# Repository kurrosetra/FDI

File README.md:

# FDI
Front Destination Indicator

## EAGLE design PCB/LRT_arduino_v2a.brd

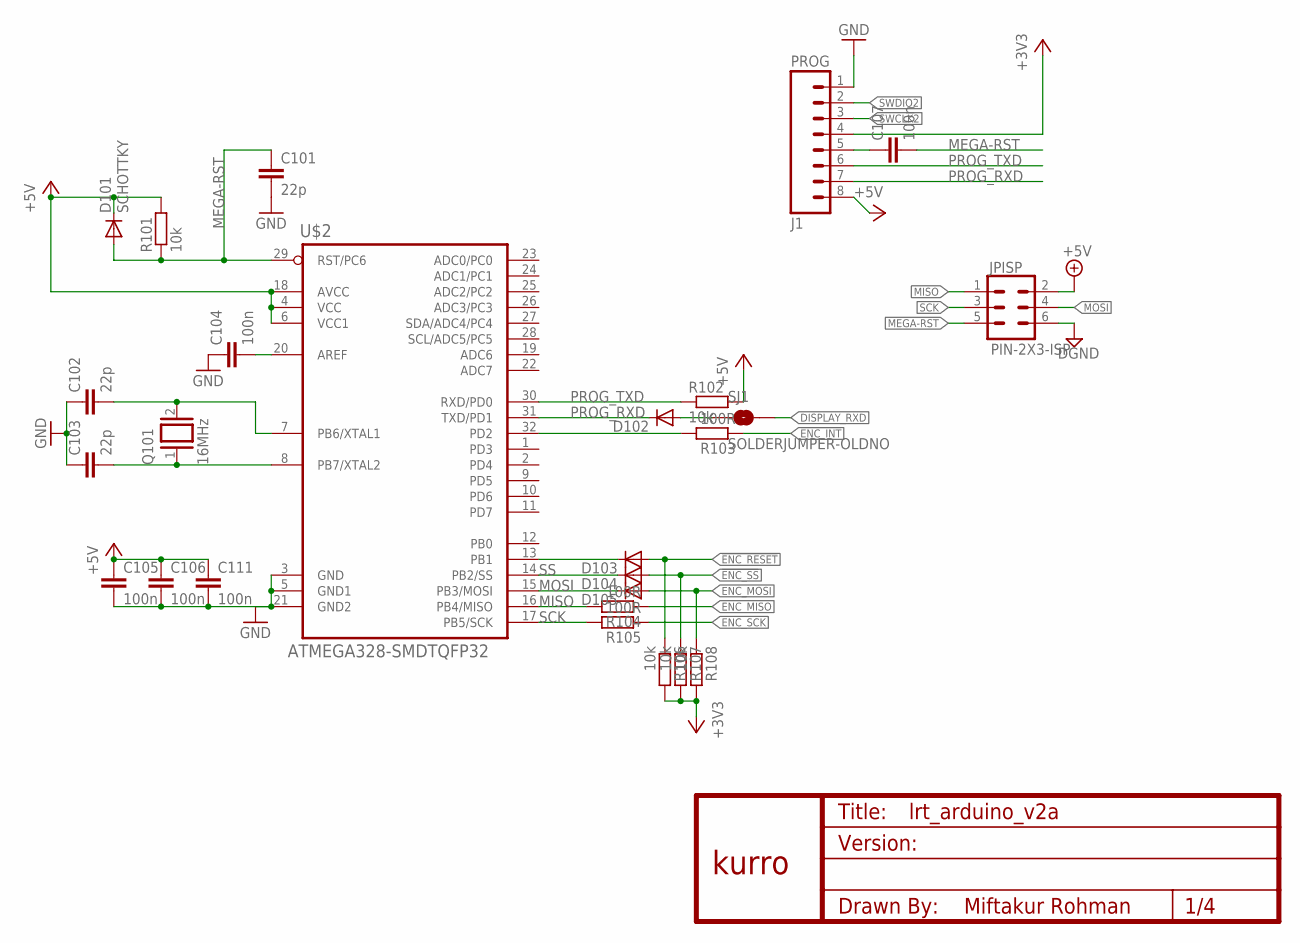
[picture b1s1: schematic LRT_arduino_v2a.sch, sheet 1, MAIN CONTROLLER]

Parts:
C101, C102, C103: 22p; C0603
C104, C105, C106, C107, C111: 100n; C0603
D101: SCHOTTKY; MICROMELF-W
D102, D103, D104, D105: DIODE-MICROMELF-W; MICROMELF-W
J1: PROG; XH-8-RA
JPISP: PIN-2X3-ISP; 2X03
Q101: 16MHz; QS
R101, R102, R106, R107, R108: 10k; R0603
R103, R104, R105: 100R; R0603
SJ1: SOLDERJUMPER-OLDNO; SJ_2S-NO
U$1: KURRO_FOOTPRINT; KURRO-LOGO
U$2: ATMEGA328-SMDTQFP32; TQFP32

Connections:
!ENC_INT: R103.1; also elsewhere on the board
!ENC_RESET: D103.A, R106.1; also elsewhere on the board
!ENC_SS: D104.A, R107.1; also elsewhere on the board
+3V3: J1.4, R106.2, R107.2, R108.2; also elsewhere on the board
+5V: C105.1, C106.1, C111.1, D101.C, J1.8, JPISP.2, R101.2, R102.2, U$2.4 (VCC), U$2.6 (VCC1), U$2.18 (AVCC); also elsewhere on the board
DISPLAY_RXD: SJ1.2; also elsewhere on the board
ENC_MISO: R104.1; also elsewhere on the board
ENC_MOSI: D105.A, R108.1; also elsewhere on the board
ENC_SCK: R105.1; also elsewhere on the board
GND: C101.2, C102.1, C103.1, C104.1, C105.2, C106.2, C111.2, J1.1, JPISP.6, U$2.3 (GND), U$2.5 (GND1), U$2.21 (GND2); also elsewhere on the board
MEGA-RST: C101.1, C107.2, D101.A, JPISP.5, R101.1, U$2.29 (RST/PC6)
MISO: JPISP.1, R104.2, U$2.16 (PB4/MISO)
MOSI: D105.C, JPISP.4, U$2.15 (PB3/MOSI)
unnamed: C104.2, U$2.20 (AREF)
unnamed: C103.2, Q101.1, U$2.8 (PB7/XTAL2)
unnamed: C102.2, Q101.2, U$2.7 (PB6/XTAL1)
unnamed: R103.2, U$2.32 (PD2)
unnamed: C107.1, J1.5
unnamed: D103.C, U$2.13 (PB1)
unnamed: D102.A, SJ1.1
PROG_RXD: D102.C, J1.7, U$2.31 (TXD/PD1)
PROG_TXD: J1.6, R102.1, U$2.30 (RXD/PD0)
SCK: JPISP.3, R105.2, U$2.17 (PB5/SCK)
SS: D104.C, U$2.14 (PB2/SS)
SWCLK2: J1.3; also elsewhere on the board
SWDIO2: J1.2; also elsewhere on the board

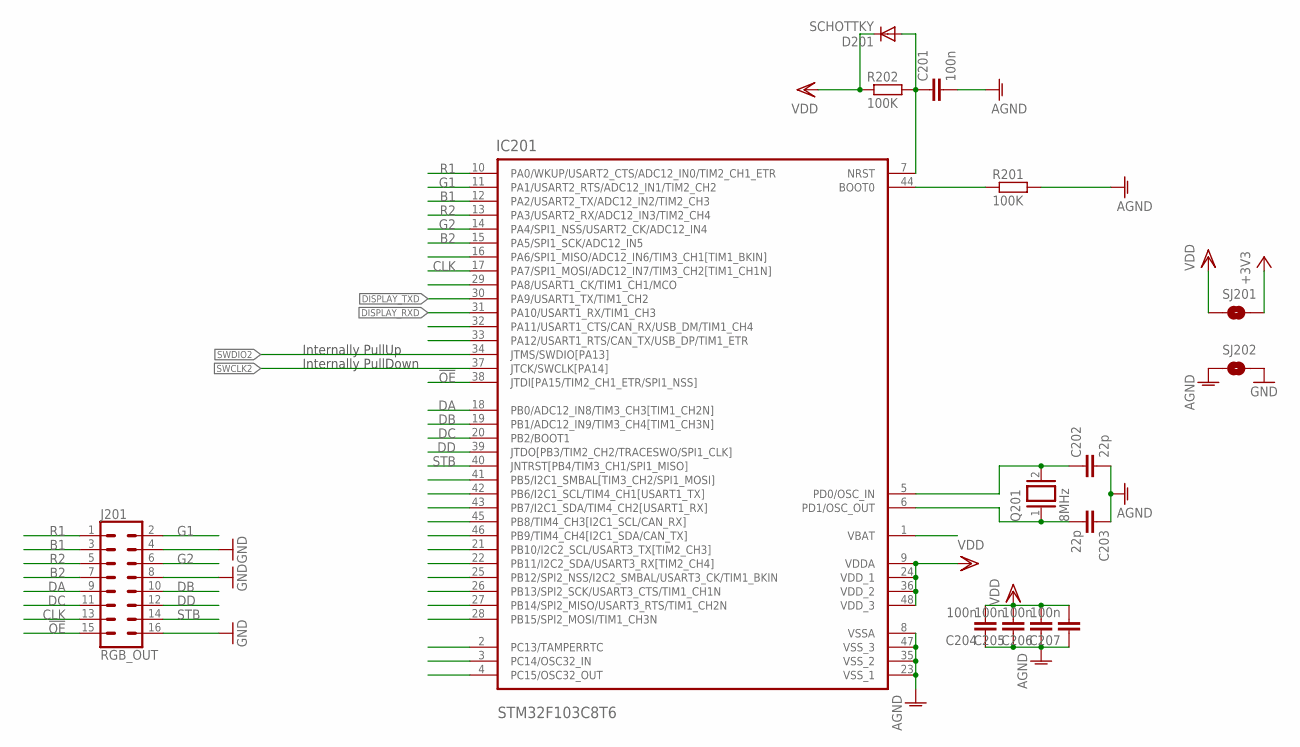
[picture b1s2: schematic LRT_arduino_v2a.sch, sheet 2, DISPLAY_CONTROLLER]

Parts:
C201, C204, C205, C206, C207: 100n; C0603
C202, C203: 22p; C0603
D201: SCHOTTKY; MICROMELF-W
IC201: STM32F103C8T6; QFP50P900X900X160-48N
J201: RGB_OUT; 2X08-LOCK
Q201: 8MHz; QS
R201, R202: 100K; R0603
SJ201, SJ202: SOLDERJUMPERTRACE; SJ_2S-TRACE

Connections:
!OE: IC201.38 (JTDI[PA15/TIM2_CH1_ETR/SPI1_NSS]), J201.15
+3V3: SJ201.2; also elsewhere on the board
AGND: C201.2, C202.2, C203.1, C204.1, C205.1, C206.1, C207.1, IC201.8 (VSSA), IC201.23 (VSS_1), IC201.35 (VSS_2), IC201.47 (VSS_3), R201.2, SJ202.1
B1: IC201.12 (PA2/USART2_TX/ADC12_IN2/TIM2_CH3), J201.3
B2: IC201.15 (PA5/SPI1_SCK/ADC12_IN5), J201.7
BOOT0: IC201.44 (BOOT0), R201.1
CLK: IC201.17 (PA7/SPI1_MOSI/ADC12_IN7/TIM3_CH2[TIM1_C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), J201.13
DA: IC201.18 (PB0/ADC12_IN8/TIM3_CH3[TIM1_CH2N]), J201.9
DB: IC201.19 (PB1/ADC12_IN9/TIM3_CH4[TIM1_CH3N]), J201.10
DC: IC201.20 (PB2/BOOT1), J201.11
DD: IC201.39 (JTDO[PB3/TIM2_CH2/TRACESWO/SPI1_CLK]), J201.12
DISPLAY_RXD: IC201.31 (PA10/USART1_RX/TIM1_CH3); also elsewhere on the board
DISPLAY_TXD: IC201.30 (PA9/USART1_TX/TIM1_CH2)
G1: IC201.11 (PA1/USART2_RTS/ADC12_IN1/TIM2_CH2), J201.2
G2: IC201.14 (PA4/SPI1_NSS/USART2_CK/ADC12_IN4), J201.6
GND: J201.4, J201.8, J201.16, SJ202.2; also elsewhere on the board
unnamed: C203.2, IC201.6 (PD1/OSC_OUT), Q201.1
unnamed: C202.1, IC201.5 (PD0/OSC_IN), Q201.2
R1: IC201.10 (PA0/WKUP/USART2_CTS/ADC12_IN0/TIM2_CH1_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), J201.1
R2: IC201.13 (PA3/USART2_RX/ADC12_IN3/TIM2_CH4), J201.5
RST: C201.1, D201.A, IC201.7 (NRST), R202.2
STB: IC201.40 (JNTRST[PB4/TIM3_CH1/SPI1_MISO]), J201.14
SWCLK2: IC201.37 (JTCK/SWCLK[PA14]); also elsewhere on the board
SWDIO2: IC201.34 (JTMS/SWDIO[PA13]); also elsewhere on the board
VDD: C204.2, C205.2, C206.2, C207.2, D201.C, IC201.9 (VDDA), IC201.24 (VDD_1), IC201.36 (VDD_2), IC201.48 (VDD_3), R202.1, SJ201.1

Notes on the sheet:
Internally PullUp
Internally PullDown

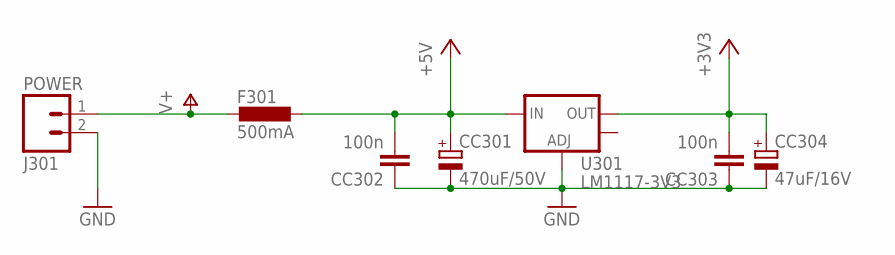
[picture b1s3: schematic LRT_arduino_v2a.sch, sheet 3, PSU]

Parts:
CC301: 470uF/50V; E2-5
CC302, CC303: 100n; C0603
CC304: 47uF/16V; E2-5
F301: 500mA; L0805
J301: POWER; XH-2-RA
U301: LM1117-3V3; SOT223

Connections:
+3V3: CC303.2, CC304.+, U301.2 (OUT); also elsewhere on the board
+5V: CC301.+, CC302.2, F301.1, U301.3 (IN); also elsewhere on the board
GND: CC301.-, CC302.1, CC303.1, CC304.-, J301.2, U301.1 (ADJ); also elsewhere on the board
V+: F301.2, J301.1

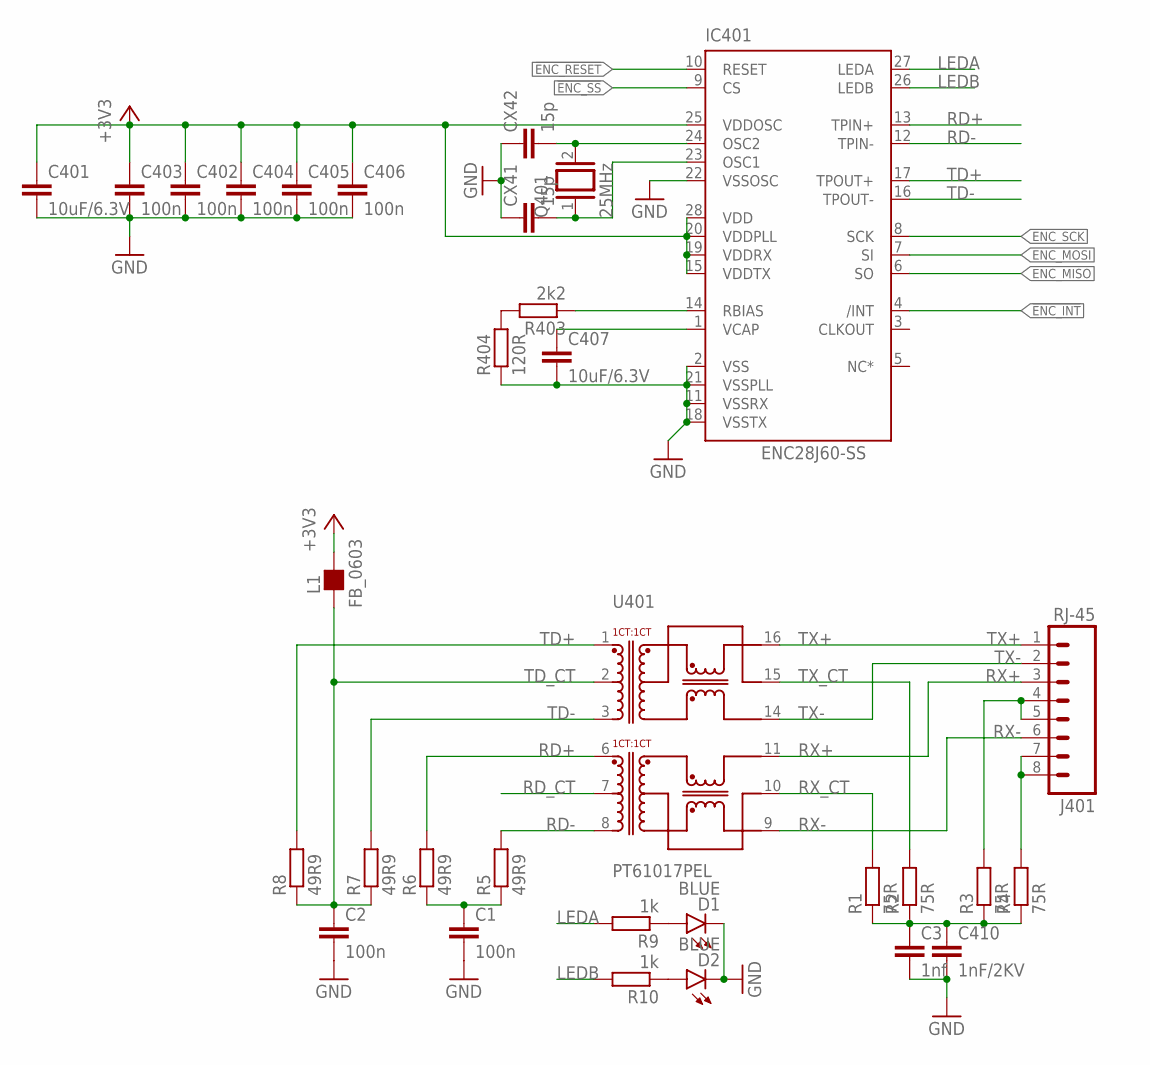
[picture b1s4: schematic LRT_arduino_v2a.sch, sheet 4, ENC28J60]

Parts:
C1, C2, C402, C403, C404, C405, C406: 100n; C0603
C3: 1nf; C0603
C401, C407: 10uF/6.3V; C0805
C410: 1nF/2KV; C050-055X075
CX41, CX42: 15p; C0603
D1, D2: BLUE; LED-1206
IC401: ENC28J60-SS; SS28
J401: RJ-45; XH-8-RA
L1: FB_0603; L0603
Q401: 25MHz; QS
R1, R2, R3, R4: 75R; R0603
R5, R6, R7, R8: 49R9; R0603
R9, R10: 1k; R0603
R403: 2k2; R0603
R404: 120R; R0603
U401: PT61017PEL; PT61017

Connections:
!ENC_INT: IC401.4 (/INT); also elsewhere on the board
!ENC_RESET: IC401.10 (RESET); also elsewhere on the board
!ENC_SS: IC401.9 (CS); also elsewhere on the board
+3V3: C401.1, C402.1, C403.1, C404.1, C405.1, C406.1, IC401.15 (VDDTX), IC401.19 (VDDRX), IC401.20 (VDDPLL), IC401.25 (VDDOSC), IC401.28 (VDD), L1.2; also elsewhere on the board
ENC_MISO: IC401.6 (SO); also elsewhere on the board
ENC_MOSI: IC401.7 (SI); also elsewhere on the board
ENC_SCK: IC401.8 (SCK); also elsewhere on the board
GND: C1.2, C2.2, C3.2, C401.2, C402.2, C403.2, C404.2, C405.2, C406.2, C407.2, C410.2, CX41.1, CX42.1, D1.C, D2.C, IC401.2 (VSS), IC401.11 (VSSRX), IC401.18 (VSSTX), IC401.21 (VSSPLL), IC401.22 (VSSOSC), R404.1; also elsewhere on the board
LEDA: IC401.27 (LEDA), R9.2
LEDB: IC401.26 (LEDB), R10.2
unnamed: D1.A, R9.1
unnamed: D2.A, R10.1
unnamed: C3.1, C410.1, R1.1, R2.1, R3.1, R4.1
unnamed 36: J401.4, J401.5, R3.2; also elsewhere on the board
unnamed: R403.2, R404.2
unnamed: C407.1, IC401.1 (VCAP)
unnamed 44: J401.7, J401.8, R4.2; also elsewhere on the board
unnamed: CX42.2, IC401.24 (OSC2), Q401.2
unnamed: CX41.2, IC401.23 (OSC1), Q401.1
unnamed: C1.1, R5.1, R6.1
unnamed: IC401.14 (RBIAS), R403.1
RD+: IC401.13 (TPIN+), R6.2, U401.6
RD-: IC401.12 (TPIN-), R5.2, U401.8
RD_CT: U401.7
RX+: J401.3, U401.11; also elsewhere on the board
RX-: J401.6, U401.9; also elsewhere on the board
RX_CT: R1.2, U401.10
TD+: IC401.17 (TPOUT+), R8.2, U401.1
TD-: IC401.16 (TPOUT-), R7.2, U401.3
TD_CT: C2.1, L1.1, R7.1, R8.1, U401.2
TX+: J401.1, U401.16; also elsewhere on the board
TX-: J401.2, U401.14; also elsewhere on the board
TX_CT: R2.2, U401.15

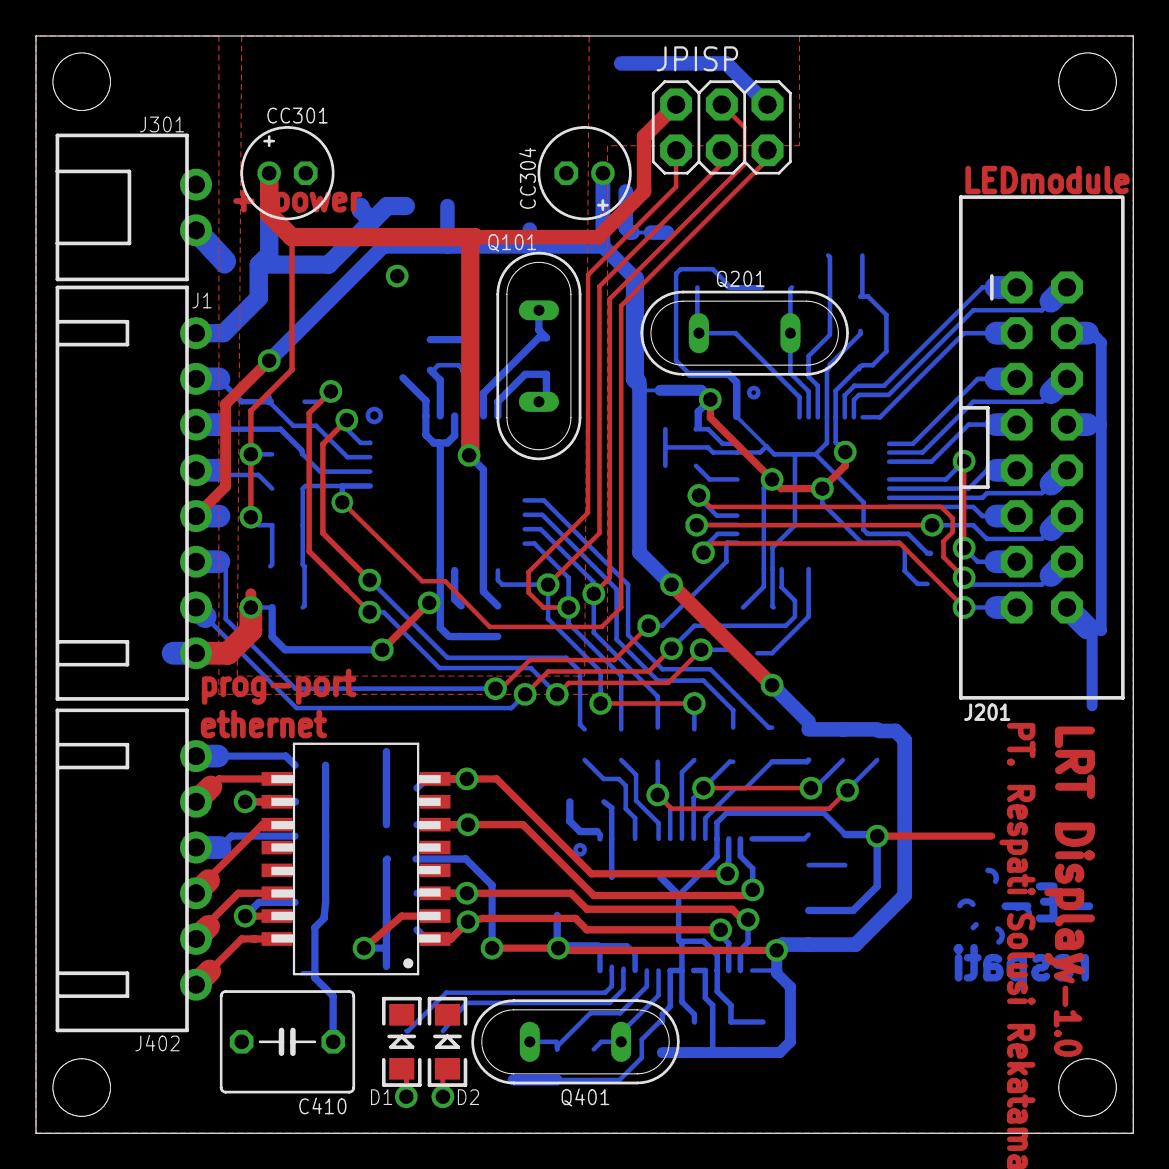
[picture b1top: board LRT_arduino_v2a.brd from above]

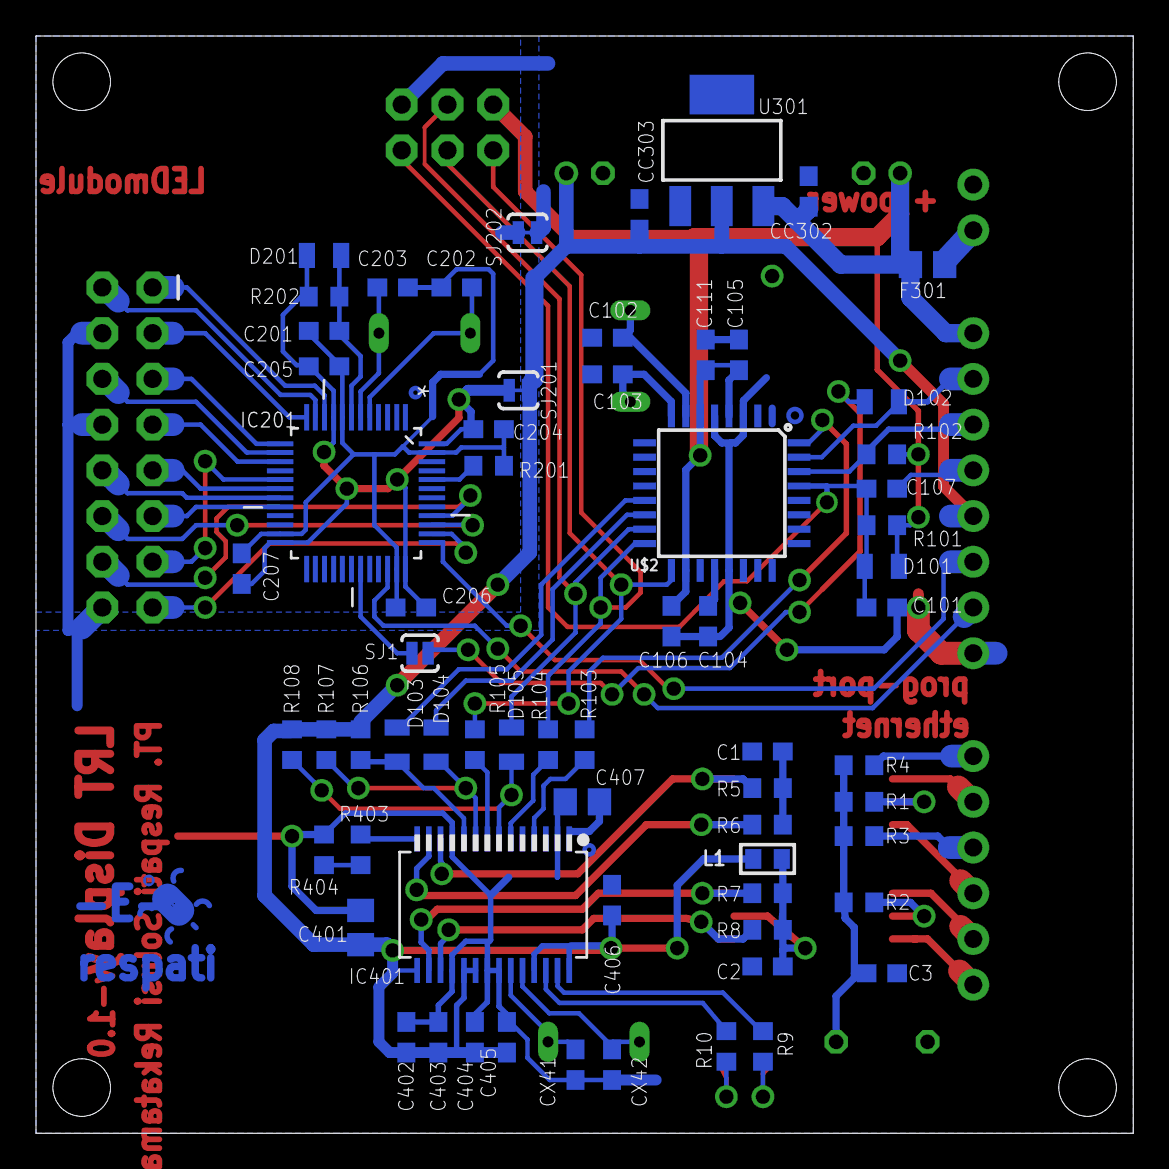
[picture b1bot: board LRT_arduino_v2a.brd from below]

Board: 2 copper layers, 61.0 x 61.0 mm, 81 parts (66 on the bottom side), 70 nets.

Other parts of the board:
J402: CONN_OUT; XH-6-RA

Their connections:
unnamed 36: J402.4; also elsewhere on the board
unnamed 44: J402.6; also elsewhere on the board
RX+: J402.3; also elsewhere on the board
RX-: J402.5; also elsewhere on the board
TX+: J402.1; also elsewhere on the board
TX-: J402.2; also elsewhere on the board

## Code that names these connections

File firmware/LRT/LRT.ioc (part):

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Mcu.Name=STM32F103C(8-B)Tx
Mcu.Package=LQFP48
Mcu.UserName=STM32F103C8Tx
PA0-WKUP.GPIOParameters=GPIO_Speed,GPIO_Label
PA0-WKUP.GPIO_Label=r1
PA0-WKUP.GPIO_Speed=GPIO_SPEED_FREQ_HIGH
PA0-WKUP.Signal=GPIO_Output
PA1.GPIOParameters=GPIO_Speed,GPIO_Label
PA1.GPIO_Label=g1
PA1.GPIO_Speed=GPIO_SPEED_FREQ_HIGH
PA1.Signal=GPIO_Output
PA10.GPIOParameters=GPIO_PuPd
PA10.GPIO_PuPd=GPIO_PULLUP
PA10.Mode=Asynchronous
PA10.Signal=USART1_RX
PA13.Mode=Serial_Wire
PA13.Signal=SYS_JTMS-SWDIO
PA14.Mode=Serial_Wire
PA14.Signal=SYS_JTCK-SWCLK
PA15.GPIOParameters=GPIO_Speed,GPIO_Label
PA15.GPIO_Label=oe
PA15.GPIO_Speed=GPIO_SPEED_FREQ_HIGH
PA15.Signal=GPIO_Output
PA2.GPIOParameters=GPIO_Speed,GPIO_Label
PA2.GPIO_Label=b1
PA2.GPIO_Speed=GPIO_SPEED_FREQ_HIGH
PA2.Signal=GPIO_Output
PA3.GPIOParameters=GPIO_Speed,GPIO_Label
PA3.GPIO_Label=r2
PA3.GPIO_Speed=GPIO_SPEED_FREQ_HIGH
PA3.Signal=GPIO_Output
PA4.GPIOParameters=GPIO_Speed,GPIO_Label
PA4.GPIO_Label=g2
PA4.GPIO_Speed=GPIO_SPEED_FREQ_HIGH
PA4.Signal=GPIO_Output
PA5.GPIOParameters=GPIO_Speed,GPIO_Label
PA5.GPIO_Label=b2
PA5.GPIO_Speed=GPIO_SPEED_FREQ_HIGH
PA5.Signal=GPIO_Output
PA7.GPIOParameters=GPIO_Speed,GPIO_PuPd,GPIO_Label,GPIO_ModeDefaultOutputPP
PA7.GPIO_Label=clk
PA7.GPIO_ModeDefaultOutputPP=GPIO_MODE_OUTPUT_PP
PA7.GPIO_PuPd=GPIO_NOPULL
PA7.GPIO_Speed=GPIO_SPEED_FREQ_HIGH
PA7.Signal=GPIO_Output
PA9.Mode=Asynchronous
PA9.Signal=USART1_TX
PB0.GPIOParameters=GPIO_Speed,GPIO_Label
PB0.GPIO_Label=da
PB0.GPIO_Speed=GPIO_SPEED_FREQ_HIGH
PB0.Signal=GPIO_Output
PB1.GPIOParameters=GPIO_Speed,GPIO_Label
PB1.GPIO_Label=db
PB1.GPIO_Speed=GPIO_SPEED_FREQ_HIGH
PB1.Signal=GPIO_Output
PB2.GPIOParameters=GPIO_Speed,GPIO_Label
PB2.GPIO_Label=dc
PB2.GPIO_Speed=GPIO_SPEED_FREQ_HIGH
PB2.Signal=GPIO_Output
PB3.GPIOParameters=GPIO_Speed,GPIO_Label
PB3.GPIO_Label=dd
PB3.GPIO_Speed=GPIO_SPEED_FREQ_HIGH
PB3.Signal=GPIO_Output
PB4.GPIOParameters=GPIO_Speed,GPIO_Label
PB4.GPIO_Label=stb
PB4.GPIO_Speed=GPIO_SPEED_FREQ_HIGH
PB4.Signal=GPIO_Output
PC13-TAMPER-RTC.GPIOParameters=GPIO_Speed,PinState,GPIO_Label
PC13-TAMPER-RTC.GPIO_Label=LED_BUILTIN
PC13-TAMPER-RTC.GPIO_Speed=GPIO_SPEED_FREQ_HIGH
PC13-TAMPER-RTC.PinState=GPIO_PIN_SET
PC13-TAMPER-RTC.Signal=GPIO_Output
PD0-OSC_IN.Mode=HSE-External-Oscillator
PD0-OSC_IN.Signal=RCC_OSC_IN
PD1-OSC_OUT.Mode=HSE-External-Oscillator
PD1-OSC_OUT.Signal=RCC_OSC_OUT
RCC.SYSCLKFreq_VALUE=72000000
RCC.SYSCLKSource=RCC_SYSCLKSOURCE_PLLCLK
board=custom

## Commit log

2020-02-21 v1.1.0
    - add initial working firmwares
    - add pcb design
    - add requirement FDI
2020-02-21 add binary
2020-08-03 rombak total struktur data
    new command format:
    $RTEXT, TYPE, param, text *
    param bits (LSB-to-MSB):
    color (3b)
    size (2b, 0->1 max 4)
    default(1b)
2020-08-05 update dmu
    changelog:
    - re-format command:
    $RTEXT, TYPE, param1, param2, "text1\ntext2" *
    - add animasi
2020-08-05 update LRT
2020-10-07 Update arduino master
    - ubah fungsi display_setting() di arduino master
    - hotfix display animation
2020-10-09 hotfix
    arduino:
    no eeprom for default_text (TODO next)

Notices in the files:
parts and their libraries:
SparkFun-Connectors: Licensing: CC v3.0 Share-Alike You are welcome to use this library for commercial purposes.
rc-master: Copyright (C) 2007, Bob Starr
SparkFun-Retired: Licensing:Creative Commons ShareAlike 4.0 International - https://creativecommons.org/licenses/by-sa/4.0
